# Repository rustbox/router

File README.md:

# Router

Rustbox builds a router!

The goal of this project is to build an open source Router from scratch, using as many open source tooling as possible.

## Goals

Desired Capabilities and Design Goals:
* 4 (or 5?) ports
* 1 Gigabit along each port
* RISC-V CPU MAC
    * A goal here, too, is to have the MAC design itself be open, as much as possible
    * Learning FPGAs is a desired outcome and would allow us to have an open CPU and Ethernet hardware

## Design

Ultimately, the Router will be components soldered on a PCB placed in a metal enclosure.

### RJ45 

Ethernet will come in via RJ45 in a 4-port connector.
    * Internal magnetics or external?

### PHY

We're currently designing the PHY portion with the MaxLinear GPY111
  * MDI from the magnetics will connect to the PHY IC
  * The PHY will convert MDI  ([Media Dependent Interface](https://en.wikipedia.org/wiki/Medium-dependent_interface)) to RGMII ([Reduced Gigabit Media Independent Interface](https://en.wikipedia.org/wiki/Media-independent_interface#RGMII))

### MAC

The MAC is the [Media Access Interface](https://en.wikipedia.org/wiki/Medium_access_control), the "brains" of the router. We're thinking of using the standard [Chipyard](https://chipyard.readthedocs.io/en/latest/) RISC-V CPU written in [Chisel](https://www.chisel-lang.org/) with our own RGMII interface, all flashed onto an FPGA.

We will also want an amount of DRAM connected to the PHY to buffer incoming and outgoing ethernet frames as needed, and for any needed storage for the (soft) SoC.

So our FPGA needs to have a certain amount of I/O pins:
* Each ethernet port needs 12 (14, including the management pins per port), so 56 pins
* 28 address, 16 data lines, plus a handful for management for DRAM
* UART
* Total: upwards of ~110 IOs available

We'd also prefer an FPGA with an open toolchain, and one with reproducible, Verilog (et al) based sources that can be generated into a bitstream just using command line tools.
 
#### Frame Size

A standard ethernet frame size is 1500 bytes. So there should be enough internal embedded memory to hold some number of frames directly in internal memory before needing to be placed in DRAM. 

Perhaps memory for Cache for the CPU?

#### DRAM

The main constraint here is total bandwidth: in order to act as a packet buffer, the FPGA needs to be able to push/pull data from the internal memory and/or DRAM at 2P*1Gbit/s minimum, where P is the port count and the doubling factor accounts for both RX & TX ("enqueue" and "dequeue") of a packet. That means for a 5-port device, we'd need a bare minimum of 10Gbps bandwidth, ignoring any lower priority besides packet buffering. 

As with all bandwidth constraints, we can "factor" that 10Gbps number into a frequency and bus width in different ways. For example:

* A bus width of 16 DDR data lanes operating at ≥312.5MHz would provide just enough raw data bandwidth:
        $$16\ \mathrm{bits}\cdot 312.5\ \mathrm{MHz}\cdot 2\ \mathrm{bits/cycle} = 10\ \mathrm{Gbps}$$

  (not accounting here for "overhead" in putting data into & taking it out of the memory)
* A bus width of 32 DDR lanes would only have to operate at half the clock rate (156.25MHz) to achieve the same data throughput, and a 64-lane-wide bus could get away with <100MHz
* A bus width of 8 SDR lanes, on the other hand, would have to operate at a brisk 1.25GHz to maintain throughput for 5 ports.

Wikipedia has a handy table ["Comparison of DDR SDRAM generations"](https://en.wikipedia.org/wiki/DDR_SDRAM#Comparison), but note that they're talking about memory _modules_ with multiple chips and implicitly assuming a bus width of 64 (and 8 bits/byte) to come up with their peak bandwidth figures. The `MT/s` column is more useful to us, since we can multiply that by a bus width to get a peak throughput in bits per second. Conveniently, any of the DDR3 or later standards seem like they would offer enough raw bandwidth for our needs with a 16-bit-wide bus. 

Attempting to account for the overhead is a challenge left up to the reader, at present. See: https://github.com/rustbox/discussion/discussions/20#discussioncomment-10400134

#### Storage

Something something SPI flash? Maybe a microSD card? We haven't looked too closely at this one yet.

#### Manufacturability

FPGAs often come in BGA format packages which is at the limit of our manufacturing capabilities. We would prefer QFN style packages or wide pitch BGA.

So far the Lattice ECP5/ECP5-5G series FPGAs seem promising: https://www.latticesemi.com/Products/FPGAandCPLD/ECP5

### Management

External serial port to interact with the system over UART
Some sort of network-accessible interface would be quite handy as well.

## Development Plan

Seth bought a BeagleV-Fire which includes a Polar Fire FPGA and an ethernet port. We'd like to experiment with the FPGA on the BeagleV to get used to those systems and also experiment with routing between multiple ethernet ports.

To make a second port we will utilize the build in SYZYGY connector which routes pins to the FPGA. We've designed a SYZYGY "pod" board which an RJ45 and PHY (GPY111) and puts RGMII over the SYZYGY connector to connect to the BeagleV FPGA. This allows us to have two ports to experiment with.

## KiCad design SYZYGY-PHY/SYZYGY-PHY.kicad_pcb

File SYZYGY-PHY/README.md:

# SYZYGY-PHY

This is an ethernet PHY board. This takes RGMII from the PHY and places it over the SYZYGY connector, intended to plug into the BeagleV-fire board.

## PCB

## Strapping Pins

The GPY111 allows different combinations of a 100 nF and various resistor values to produce different 4 bit values in the pin strapping configurations.

There are three strapping pin inputs, LED0, LED1, and LED2 giving 12 bits in total configuration information.

The below **Table 15** (page 42) shows how each Capacitor/Resistor combination forms to produce a 4 bit value

**Table 16** (page 42) and Table 17 (page 43, not shown here) shows the meaning of each bit

For our implementation:

`MDIO[4:0] = 0bABCDE` where `MDIO` is the address to use to talk to the PHY using the MDIO interface. Each of A, B, C, D, and E are bit variables, can be freely chosen to be 0 or 1, forming the "address".
    
`FLOW = 0` where `FLOW` means we're connecting to 1000BASE-T

`MODE[1:0] = 0b00` where `MODE` means we're talking RGMII to the MAC

`CONF[1:0] = 0b11` where `CONF` means 0 ns skew between Clock and Data for both Rx and Tx

`ANEG[1:0] = 0b00` where `ANEG` concerns auto negotiation of speeds. `0b00` means that the GPY111 will automatically go between 10/100/1000 Mbps.

So this means:

    LED0 = 0bBCDE
    LED1 = 0bA000
    LED2 = 0b1100

Therefore:
* LED0: resistor and capacitor should be chosen based on the pattern of `0bBCDE`
* LED1: resistor value should be 11.0 kOhm, And if A=0 then no capacitor, and if A=1 then use a 100 nF capacitor
* LED2: resistor value should be 3.92 kOhm, with a 100 nF capacitor

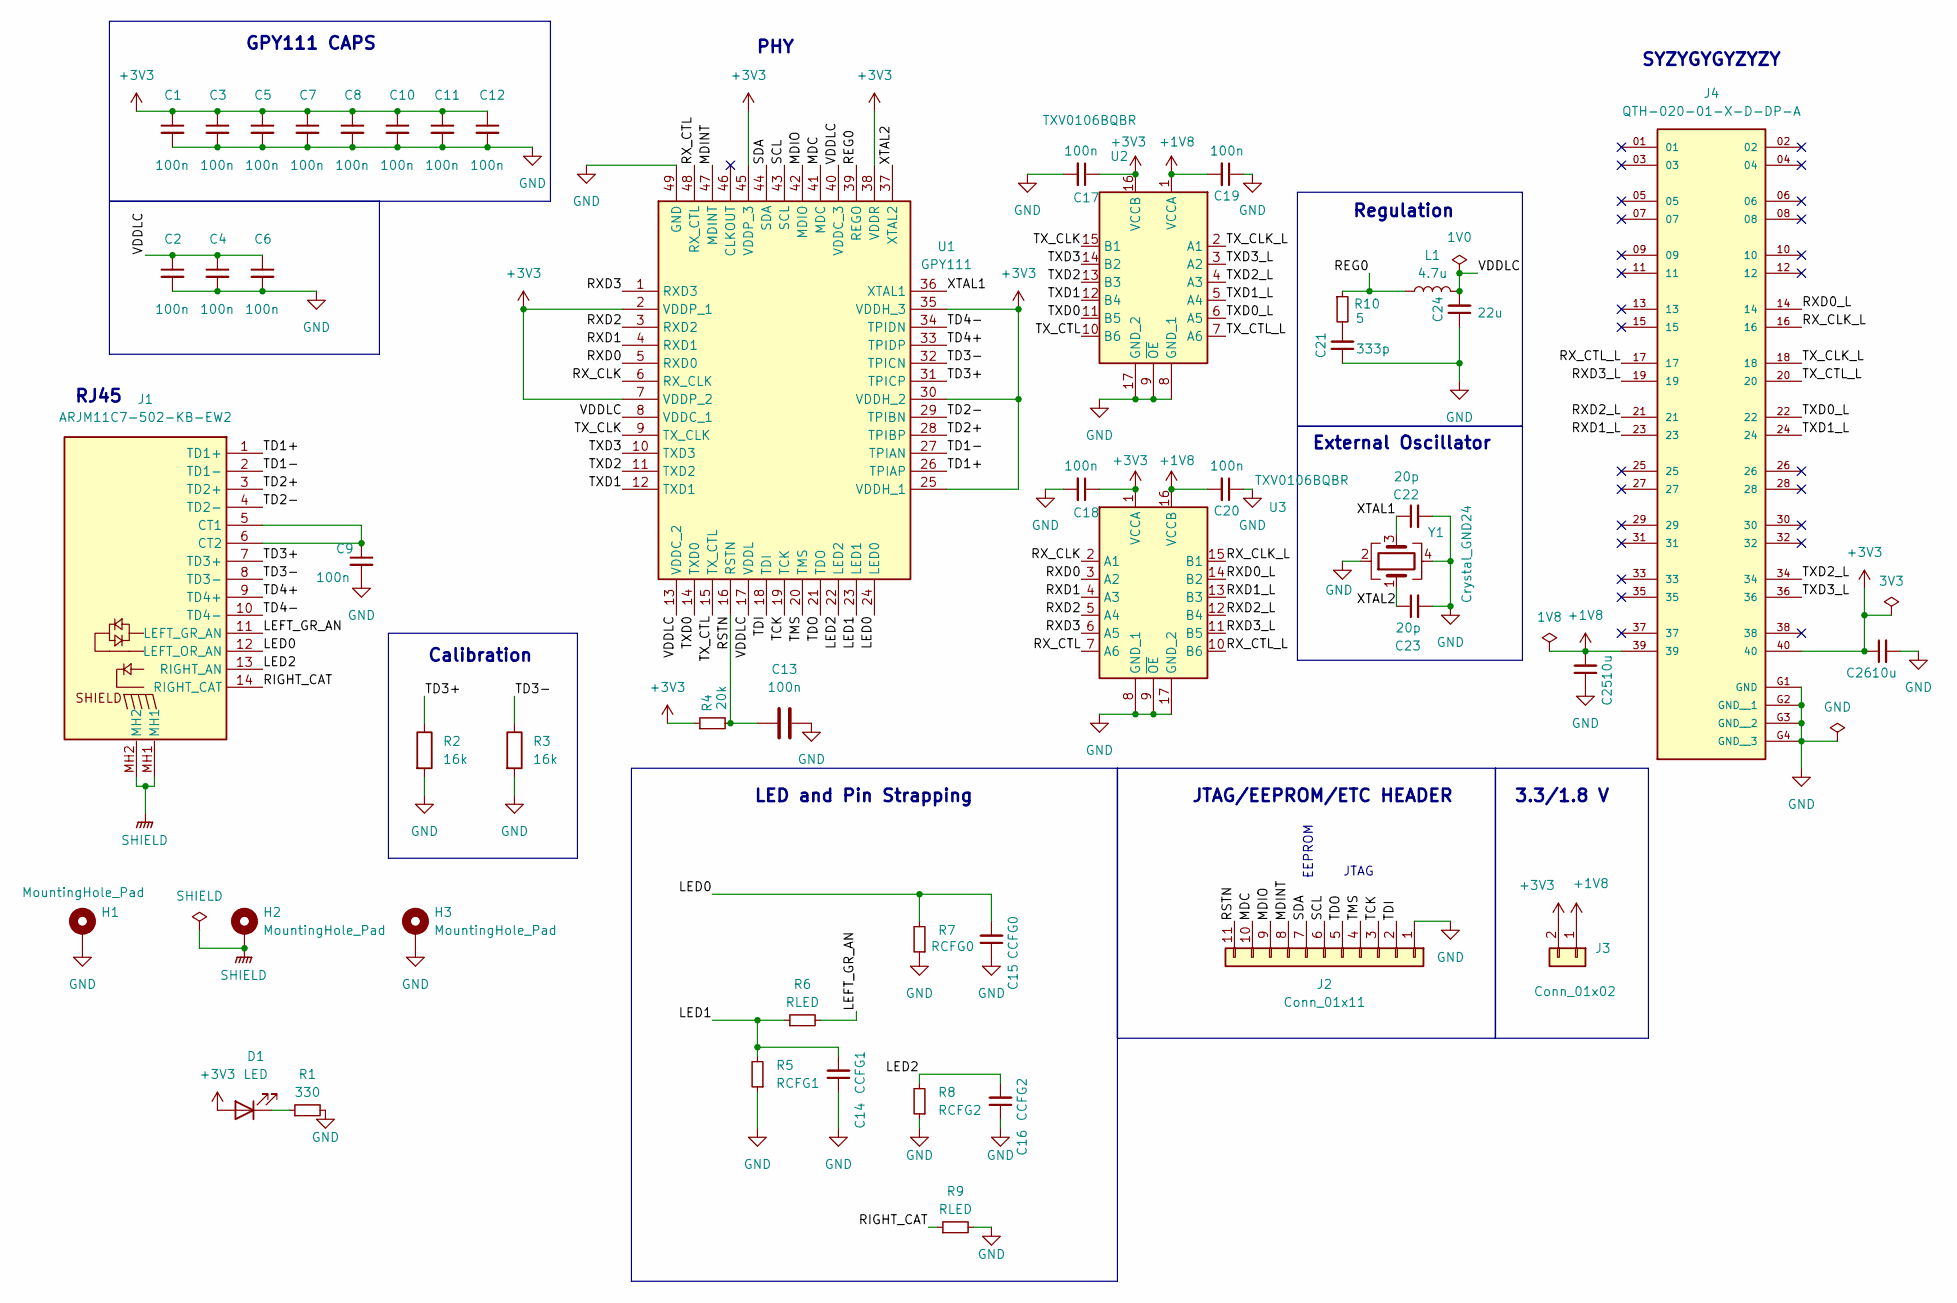
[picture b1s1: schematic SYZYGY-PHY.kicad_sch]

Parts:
C1, C2, C3, C4, C5, C6, C7, C8, C9, C10, C11, C12, C13, C17, C18, C19, C20: 100n; C_0805_2012Metric_Pad1.18x1.45mm_HandSolder
C14: CCFG1; C_0805_2012Metric_Pad1.18x1.45mm_HandSolder
C15: CCFG0; C_0805_2012Metric_Pad1.18x1.45mm_HandSolder
C16: CCFG2; C_0805_2012Metric_Pad1.18x1.45mm_HandSolder
C21: 333p; C_0805_2012Metric_Pad1.18x1.45mm_HandSolder
C22, C23: 20p; C_0805_2012Metric_Pad1.18x1.45mm_HandSolder
C24: 22u; C_0805_2012Metric_Pad1.18x1.45mm_HandSolder
C25, C26: 10u; C_0805_2012Metric_Pad1.18x1.45mm_HandSolder
D1: LED; LED_0805_2012Metric; Mouser # 710-150080VS75000
H1, H2, H3: MountingHole_Pad; MountingHole_2.7mm_M2.5_Pad
J1: ARJM11C7-502-KB-EW2; ARJM11C7502KBEW2; Mouser Part Number 815-RJM11C7502KBEW2
J2: Conn_01x11; PinSocket_1x11_P2.54mm_Vertical; Mouser # 538-22-15-2116
J3: Conn_01x02; PinHeader_1x02_P2.54mm_Vertical
J4: QTH-020-01-X-D-DP-A; SAMTEC_QTH-020-01-X-D-DP-A; PARTREV L; Mouser # 200-QTH02001LDDPA
L1: 4.7u; Inductor 0806 (2016 metric); Part MAKK2016T4R7M
R1: 330; R_0805_2012Metric_Pad1.20x1.40mm_HandSolder
R2: 16k; R_0805_2012Metric_Pad1.20x1.40mm_HandSolder; Mouser # 667-ERJ-6ENF1602V
R3: 16k; R_0805_2012Metric_Pad1.20x1.40mm_HandSolder
R4: 20k; R_0805_2012Metric_Pad1.20x1.40mm_HandSolder
R5: RCFG1; R_0805_2012Metric_Pad1.20x1.40mm_HandSolder
R6, R9: RLED; R_0805_2012Metric_Pad1.20x1.40mm_HandSolder
R7: RCFG0; R_0805_2012Metric_Pad1.20x1.40mm_HandSolder
R8: RCFG2; R_0805_2012Metric_Pad1.20x1.40mm_HandSolder
R10: 5; R_0805_2012Metric_Pad1.20x1.40mm_HandSolder
U1: GPY111; QFN50P700X700X90-49N-D; Mouser Part Number 701-GPY111
U2, U3: TXV0106BQBR; Mouser Part Number 595-TXV0106BQBR
Y1: Crystal_GND24; Crystal_SMD_3225-4Pin_3.2x2.5mm_HandSoldering; Manufacturer # TSX-3225 25.0000MF18X-G0; Mouser 732-TSX-322MF18X-G

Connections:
+1V8: C19.2, C20.2, C25.2, J3.1, J4.39, U2.1 (VCCA), U3.16 (VCCB)
+3V3: C1.1, C3.1, C5.1, C7.1, C8.1, C10.1, C11.1, C12.1, C17.1, C18.1, C26.1, D1.2 (A), J3.2, J4.40, R4.1, U1.2 (VDDP_1), U1.7 (VDDP_2), U1.25 (VDDH_1), U1.30 (VDDH_2), U1.35 (VDDH_3), U1.38 (VDDR), U1.45 (VDDP_3), U2.16 (VCCB), U3.1 (VCCA)
/LED0: C15.2, J1.12 (LEFT_OR_AN), R7.2, U1.24 (LED0)
/LED1: C14.2, R5.2, R6.1, U1.23 (LED1)
/LED2: C16.2, J1.13 (RIGHT_AN), R8.2, U1.22 (LED2)
/LEFT_GR_AN: J1.11 (LEFT_GR_AN), R6.2
/MDC: J2.10, U1.41 (MDC)
/MDINT: J2.8, U1.47 (MDINT)
/MDIO: J2.9, U1.42 (MDIO)
/REG0: L1.1, R10.1, U1.39 (REGO)
/RIGHT_CAT: J1.14 (RIGHT_CAT), R9.1
/RSTN: C13.2, J2.11, R4.2, U1.16 (RSTN)
/RXD0: U1.5 (RXD0), U3.3 (A2)
/RXD0_L: J4.14, U3.14 (B2)
/RXD1: U1.4 (RXD1), U3.4 (A3)
/RXD1_L: J4.23, U3.13 (B3)
/RXD2: U1.3 (RXD2), U3.5 (A4)
/RXD2_L: J4.21, U3.12 (B4)
/RXD3: U1.1 (RXD3), U3.6 (A5)
/RXD3_L: J4.19, U3.11 (B5)
/RX_CLK: U1.6 (RX_CLK), U3.2 (A1)
/RX_CLK_L: J4.16, U3.15 (B1)
/RX_CTL: U1.48 (RX_CTL), U3.7 (A6)
/RX_CTL_L: J4.17, U3.10 (B6)
/SCL: J2.6, U1.43 (SCL)
/SDA: J2.7, U1.44 (SDA)
/TCK: J2.3, U1.19 (TCK)
/TD1+: J1.1 (TD1+), U1.26 (TPIAP)
/TD1-: J1.2 (TD1-), U1.27 (TPIAN)
/TD2+: J1.3 (TD2+), U1.28 (TPIBP)
/TD2-: J1.4 (TD2-), U1.29 (TPIBN)
/TD3+: J1.7 (TD3+), R2.1, U1.31 (TPICP)
/TD3-: J1.8 (TD3-), R3.1, U1.32 (TPICN)
/TD4+: J1.9 (TD4+), U1.33 (TPIDP)
/TD4-: J1.10 (TD4-), U1.34 (TPIDN)
/TDI: J2.2, U1.18 (TDI)
/TDO: J2.5, U1.21 (TDO)
/TMS: J2.4, U1.20 (TMS)
/TXD0: U1.14 (TXD0), U2.11 (B5)
/TXD0_L: J4.22, U2.6 (A5)
/TXD1: U1.12 (TXD1), U2.12 (B4)
/TXD1_L: J4.24, U2.5 (A4)
/TXD2: U1.11 (TXD2), U2.13 (B3)
/TXD2_L: J4.34, U2.4 (A3)
/TXD3: U1.10 (TXD3), U2.14 (B2)
/TXD3_L: J4.36, U2.3 (A2)
/TX_CLK: U1.9 (TX_CLK), U2.15 (B1)
/TX_CLK_L: J4.18, U2.2 (A1)
/TX_CTL: U1.15 (TX_CTL), U2.10 (B6)
/TX_CTL_L: J4.20, U2.7 (A6)
/VDDLC: C2.1, C4.1, C6.1, C24.2, L1.2, U1.8 (VDDC_1), U1.13 (VDDC_2), U1.17 (VDDL), U1.40 (VDDC_3)
/XTAL1: C22.1, U1.36 (XTAL1), Y1.3
/XTAL2: C23.1, U1.37 (XTAL2), Y1.1
GND: C1.2, C2.2, C3.2, C4.2, C5.2, C6.2, C7.2, C8.2, C9.2, C10.2, C11.2, C12.2, C13.1, C14.1, C15.1, C16.1, C17.2, C18.2, C19.1, C20.1, C21.1, C22.2, C23.2, C24.1, C25.1, C26.2, H1.1, H3.1, J2.1, J4.G1 (GND), J4.G2 (GND__1), J4.G3 (GND__2), J4.G4 (GND__3), R1.2, R2.2, R3.2, R5.1, R7.1, R8.1, R9.2, U1.49 (GND), U2.8 (GND_1), U2.9 (~OE), U2.17 (GND_2), U3.8 (GND_1), U3.9 (~OE), U3.17 (GND_2), Y1.2, Y1.4
unnamed: C21.2, R10.2
unnamed: D1.1 (K), R1.1
unnamed: C9.1, J1.5 (CT1), J1.6 (CT2)
SHIELD: H2.1, J1.MH1, J1.MH2

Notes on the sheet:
JTAG/EEPROM/ETC HEADER
PHY
GPY111 CAPS
LED and Pin Strapping
RJ45
EEPROM
Regulation
Calibration
SYZYGYGYZYZY
3.3/1.8 V
JTAG
External Oscillator

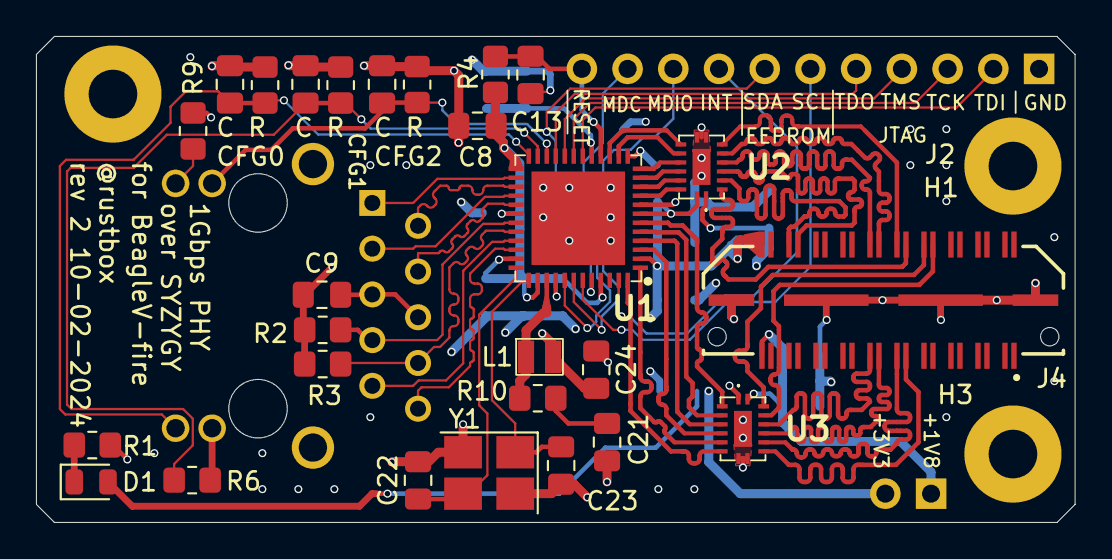
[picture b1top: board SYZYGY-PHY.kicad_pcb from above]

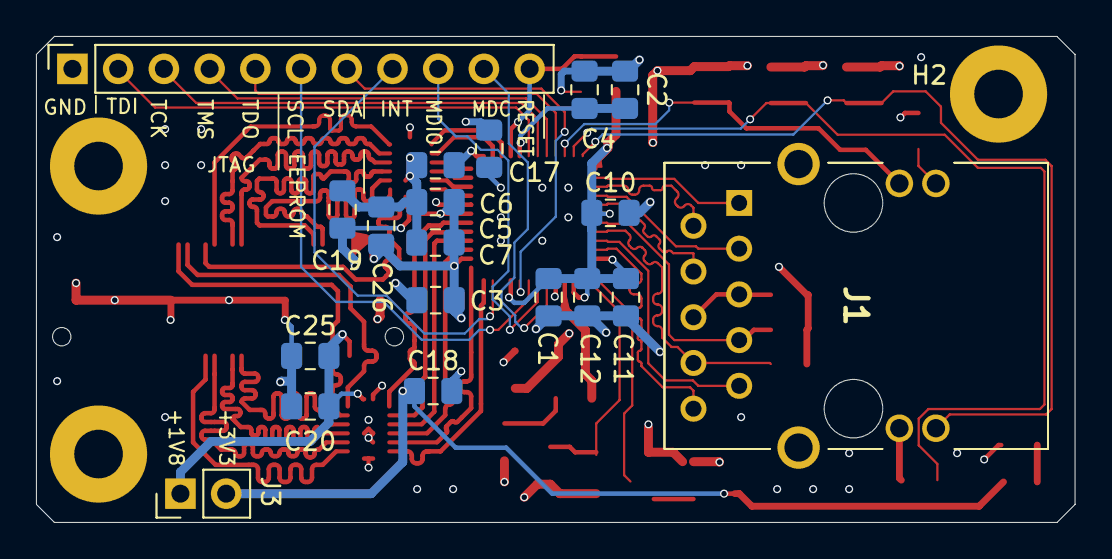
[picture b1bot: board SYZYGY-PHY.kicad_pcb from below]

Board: 4 copper layers, 57.7 x 27.0 mm, 49 parts (19 on the bottom side), 58 nets.

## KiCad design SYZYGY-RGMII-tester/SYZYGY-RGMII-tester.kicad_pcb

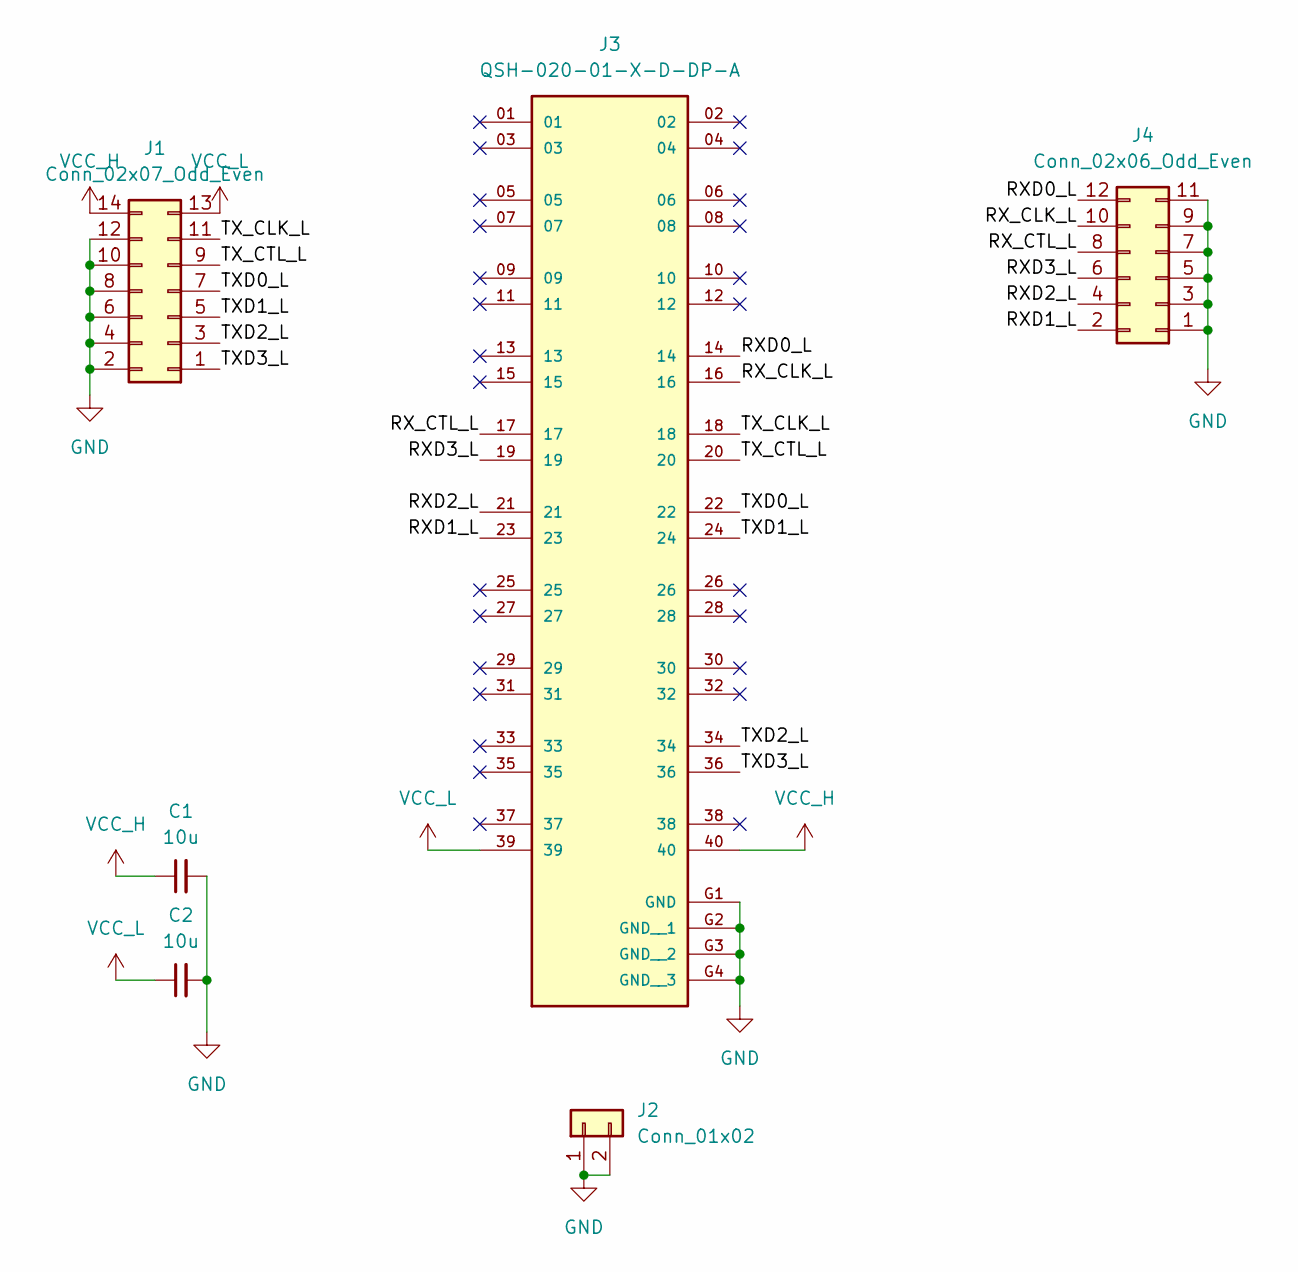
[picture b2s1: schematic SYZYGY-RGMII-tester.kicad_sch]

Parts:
C1, C2: 10u; C_0805_2012Metric
J1: Conn_02x07_Odd_Even; PinHeader_2x07_P2.54mm_Vertical
J2: Conn_01x02; PinHeader_1x02_P2.54mm_Horizontal
J3: QSH-020-01-X-D-DP-A; SAMTEC_QSH-020-01-X-D-DP-A; PARTREV M
J4: Conn_02x06_Odd_Even; PinHeader_2x06_P2.54mm_Vertical

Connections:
/RXD0_L: J3.14, J4.12
/RXD1_L: J3.23, J4.2
/RXD2_L: J3.21, J4.4
/RXD3_L: J3.19, J4.6
/RX_CLK_L: J3.16, J4.10
/RX_CTL_L: J3.17, J4.8
/TXD0_L: J1.7, J3.22
/TXD1_L: J1.5, J3.24
/TXD2_L: J1.3, J3.34
/TXD3_L: J1.1, J3.36
/TX_CLK_L: J1.11, J3.18
/TX_CTL_L: J1.9, J3.20
GND: C1.2, C2.2, J1.2, J1.4, J1.6, J1.8, J1.10, J1.12, J2.1, J2.2, J3.G1 (GND), J3.G2 (GND__1), J3.G3 (GND__2), J3.G4 (GND__3), J4.1, J4.3, J4.5, J4.7, J4.9, J4.11
VCC_H: C1.1, J1.14, J3.40
VCC_L: C2.1, J1.13, J3.39

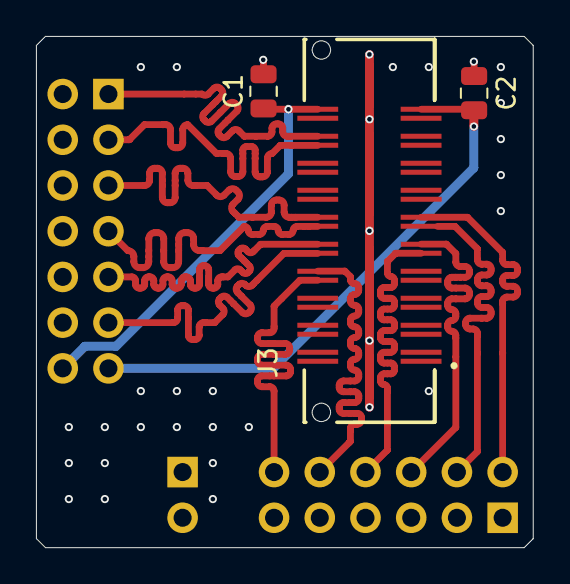
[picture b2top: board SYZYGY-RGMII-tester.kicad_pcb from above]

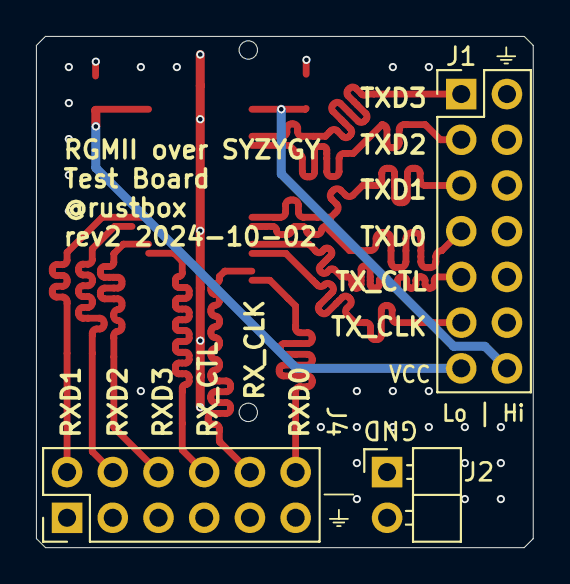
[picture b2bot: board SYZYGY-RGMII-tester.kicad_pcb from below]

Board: 4 copper layers, 27.6 x 28.4 mm, 6 parts (3 on the bottom side), 15 nets.

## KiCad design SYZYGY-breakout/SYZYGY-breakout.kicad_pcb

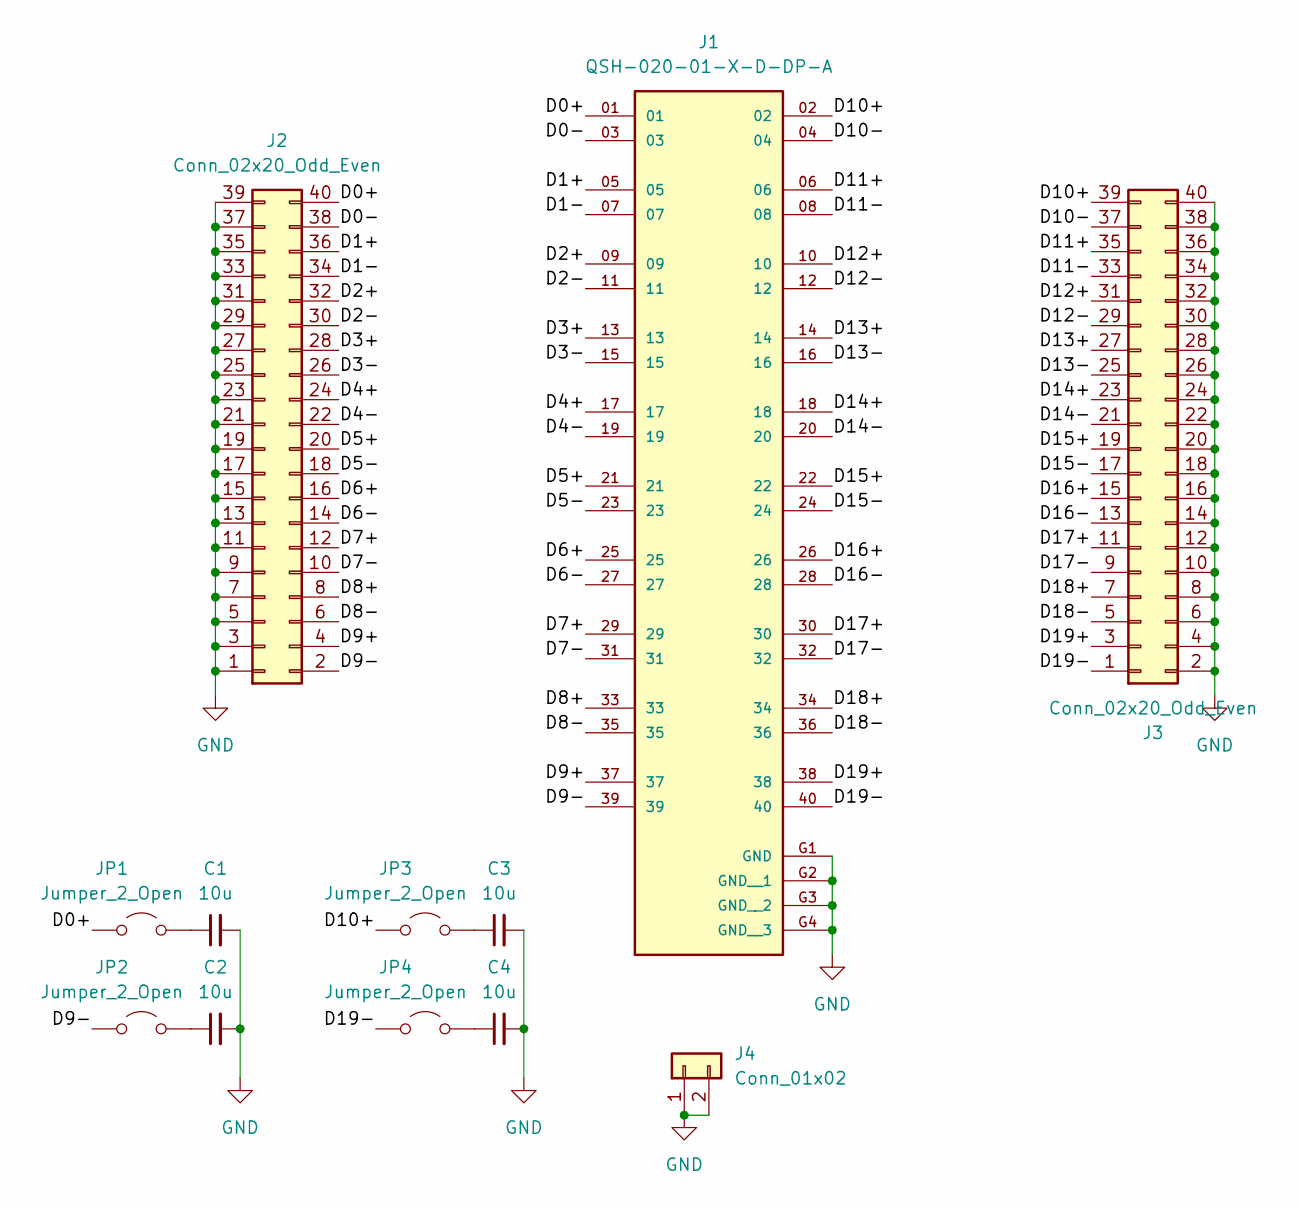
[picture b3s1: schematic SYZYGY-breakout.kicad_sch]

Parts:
C1, C2, C3, C4: 10u; C_0805_2012Metric
J1: QSH-020-01-X-D-DP-A; SAMTEC_QSH-020-01-X-D-DP-A; PARTREV M
J2, J3: Conn_02x20_Odd_Even; PinHeader_2x20_P2.54mm_Vertical
J4: Conn_01x02; PinHeader_1x02_P2.54mm_Horizontal
JP1, JP2, JP3, JP4: Jumper_2_Open; TestPoint_2Pads_Pitch2.54mm_Drill0.8mm

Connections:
/D0+: J1.01, J2.40, JP1.1 (A)
/D0-: J1.03, J2.38
/D1+: J1.05, J2.36
/D1-: J1.07, J2.34
/D2+: J1.09, J2.32
/D2-: J1.11, J2.30
/D3+: J1.13, J2.28
/D3-: J1.15, J2.26
/D4+: J1.17, J2.24
/D4-: J1.19, J2.22
/D5+: J1.21, J2.20
/D5-: J1.23, J2.18
/D6+: J1.25, J2.16
/D6-: J1.27, J2.14
/D7+: J1.29, J2.12
/D7-: J1.31, J2.10
/D8+: J1.33, J2.8
/D8-: J1.35, J2.6
/D9+: J1.37, J2.4
/D9-: J1.39, J2.2, JP2.1 (A)
/D10+: J1.02, J3.39, JP3.1 (A)
/D10-: J1.04, J3.37
/D11+: J1.06, J3.35
/D11-: J1.08, J3.33
/D12+: J1.10, J3.31
/D12-: J1.12, J3.29
/D13+: J1.14, J3.27
/D13-: J1.16, J3.25
/D14+: J1.18, J3.23
/D14-: J1.20, J3.21
/D15+: J1.22, J3.19
/D15-: J1.24, J3.17
/D16+: J1.26, J3.15
/D16-: J1.28, J3.13
/D17+: J1.30, J3.11
/D17-: J1.32, J3.9
/D18+: J1.34, J3.7
/D18-: J1.36, J3.5
/D19+: J1.38, J3.3
/D19-: J1.40, J3.1, JP4.1 (A)
GND: C1.2, C2.2, C3.2, C4.2, J1.G1 (GND), J1.G2 (GND__1), J1.G3 (GND__2), J1.G4 (GND__3), J2.1, J2.3, J2.5, J2.7, J2.9, J2.11, J2.13, J2.15, J2.17, J2.19, J2.21, J2.23, J2.25, J2.27, J2.29, J2.31, J2.33, J2.35, J2.37, J2.39, J3.2, J3.4, J3.6, J3.8, J3.10, J3.12, J3.14, J3.16, J3.18, J3.20, J3.22, J3.24, J3.26, J3.28, J3.30, J3.32, J3.34, J3.36, J3.38, J3.40, J4.1, J4.2
unnamed: C1.1, JP1.2 (B)
unnamed: C2.1, JP2.2 (B)
unnamed: C3.1, JP3.2 (B)
unnamed: C4.1, JP4.2 (B)

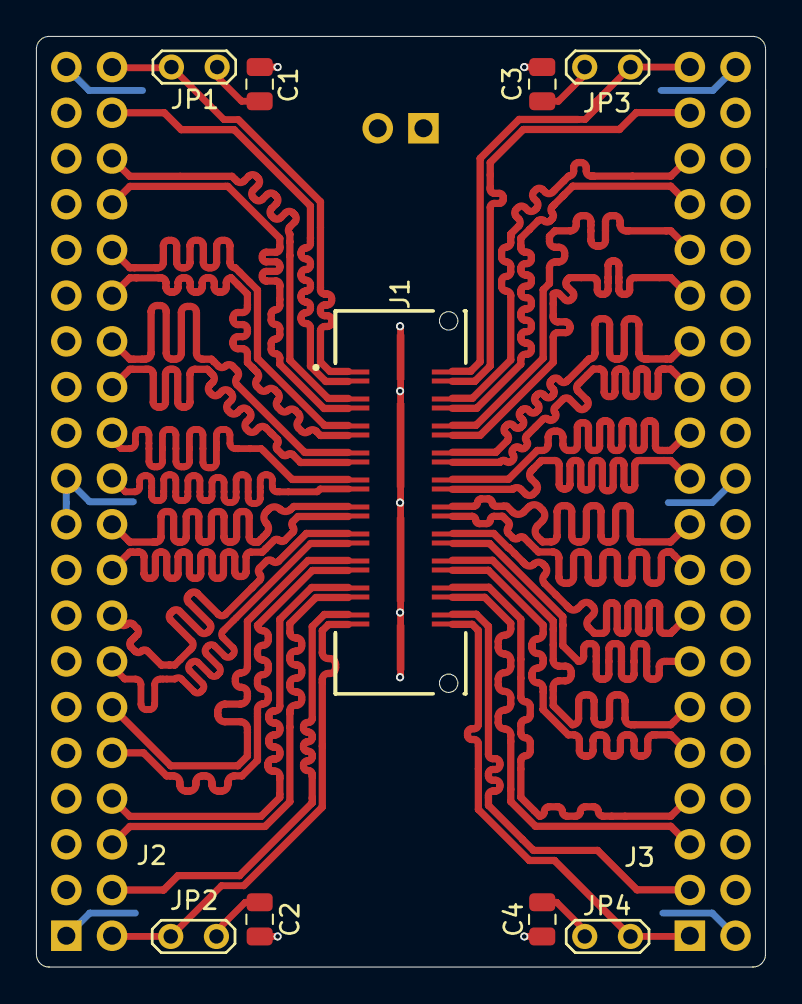
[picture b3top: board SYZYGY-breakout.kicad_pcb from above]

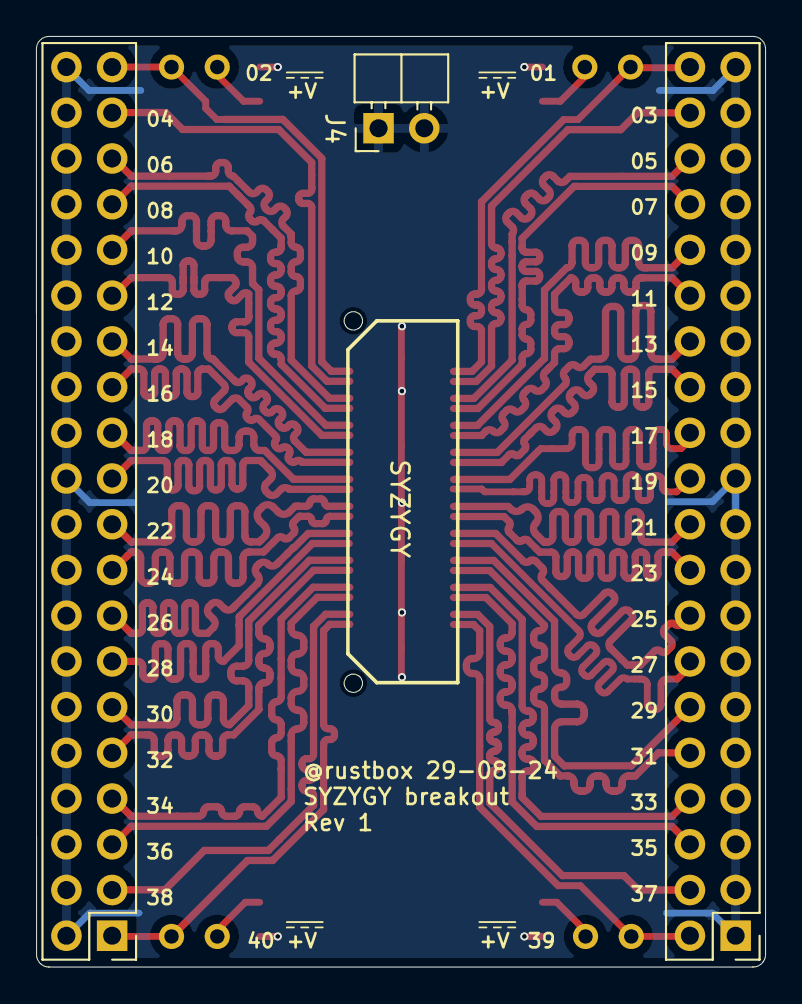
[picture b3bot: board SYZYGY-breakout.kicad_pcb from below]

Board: 2 copper layers, 40.5 x 51.7 mm, 12 parts (3 on the bottom side), 45 nets.
